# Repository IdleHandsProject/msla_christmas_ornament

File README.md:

# Christmas Ornament 3D printing Christmas Ornament

A Christmas ornament that 3D prints other Christmas ornaments!

Check out the video below!
[https://youtu.be/VCcJjI2u4AU](https://youtu.be/VCcJjI2u4AU)

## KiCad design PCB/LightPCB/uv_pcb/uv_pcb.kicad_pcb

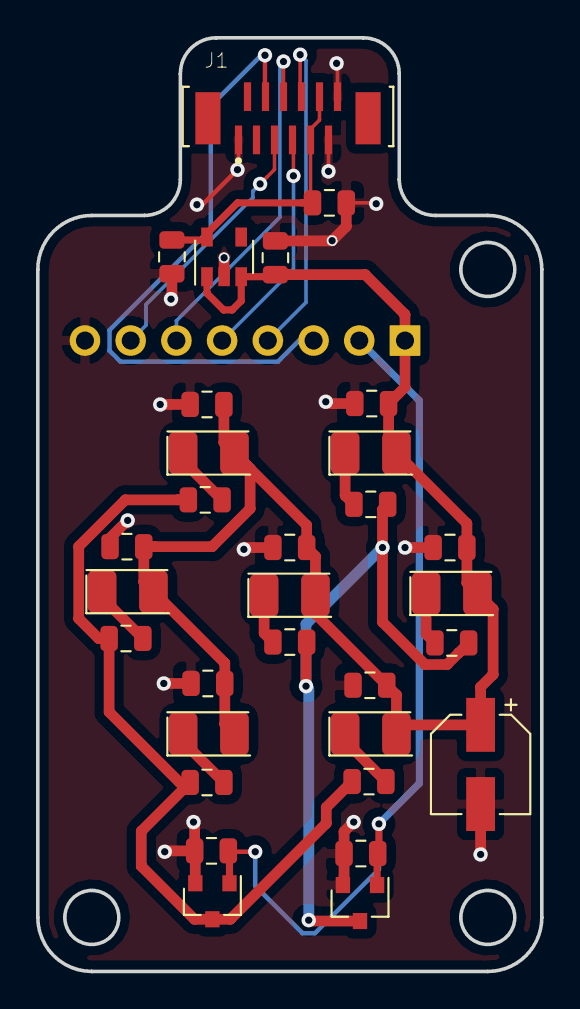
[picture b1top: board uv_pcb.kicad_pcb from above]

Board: 2 copper layers, 28.0 x 51.9 mm, 32 parts (1 on the bottom side), 18 nets.

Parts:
C1: 100uF; CP_Elec_5x5.3
C2, C4, C5, C6, C7, C8, C9, C10, C11: 1uF; C_0805_2012Metric
C3: 2.2uF; C_0805_2012Metric
D1, D2, D3, D4, D5, D6, D7: uv_led; vlmu3100
J1: Conn_01x12; TE_1-1734742-2
J2: Conn_01x08; PinHeader_1x08_P2.54mm_Horizontal
Q1, Q2: 2N7002; SOT-23
R1, R2, R3, R4, R5, R6, R7: 200R; R_0805_2012Metric
R8, R9: 10k; R_0805_2012Metric
U1: AP2112K-3.3V; SOT-23-5

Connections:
+3V3: C3.1, C4.1, J1.9, J1.10, U1.5
+5V: C1.1, C2.1, C5.1, C6.1, C7.1, C8.1, C9.1, C10.1, C11.1, D1.2, D2.2, D3.2, D4.2, D5.2, D6.2, D7.2, J2.1, U1.1, U1.3
CLK: J1.6, J2.6
CS: J1.8, J2.4
DC: J1.7, J2.5
GND: C1.2, C2.2, C3.2, C4.2, C5.2, C6.2, C7.2, C8.2, C9.2, C10.2, C11.2, J1.1, J1.11, J1.12, J2.8, Q1.2, Q2.2, R8.1, R9.1, U1.2
MOSI: J1.5, J2.7
unnamed: D1.1, R1.2
unnamed: D2.1, R2.2
unnamed: D3.1, R3.2
unnamed: D4.1, R4.2
unnamed: D5.1, R5.2
unnamed: D6.1, R6.2
unnamed: D7.1, R7.2
unnamed: Q1.3, R1.1, R2.1, R3.1
unnamed: Q2.3, R4.1, R5.1, R6.1, R7.1
RST: J1.4, J2.3
SW1: J2.2, Q1.1, Q2.1, R8.2, R9.2

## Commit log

2018-12-24 updated Ball Top
2018-12-24 added reset to PCB
2018-12-28 Use Google++ style
    Added .clang-format so that VScode and other tools can autoformat the source. Applied the Google code style as it is the closest to the existing codebase. Added #defines for the printing states.
2018-12-28 Capitialization
    Spotted another titlecase variable
2018-12-29 Added video link to README
